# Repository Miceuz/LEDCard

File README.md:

LEDCard
=======

A business card with blinky leds

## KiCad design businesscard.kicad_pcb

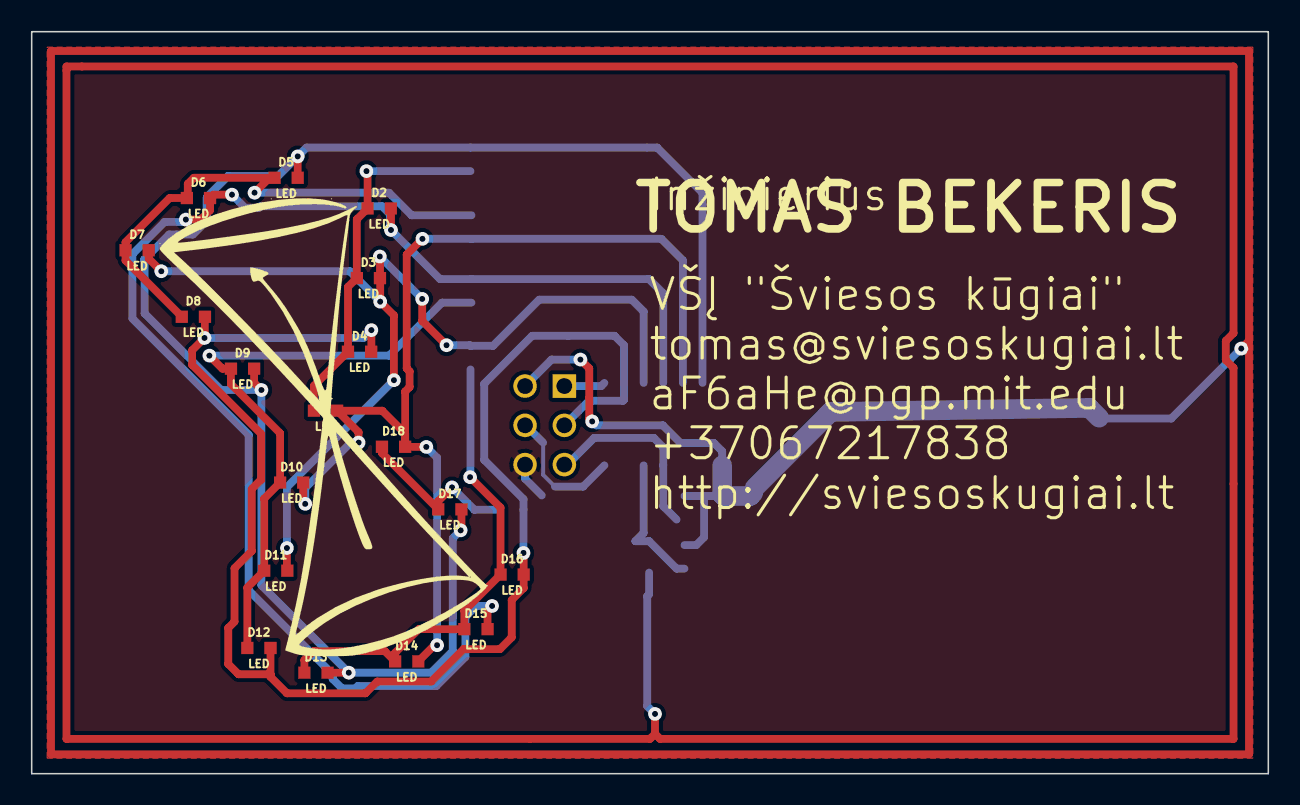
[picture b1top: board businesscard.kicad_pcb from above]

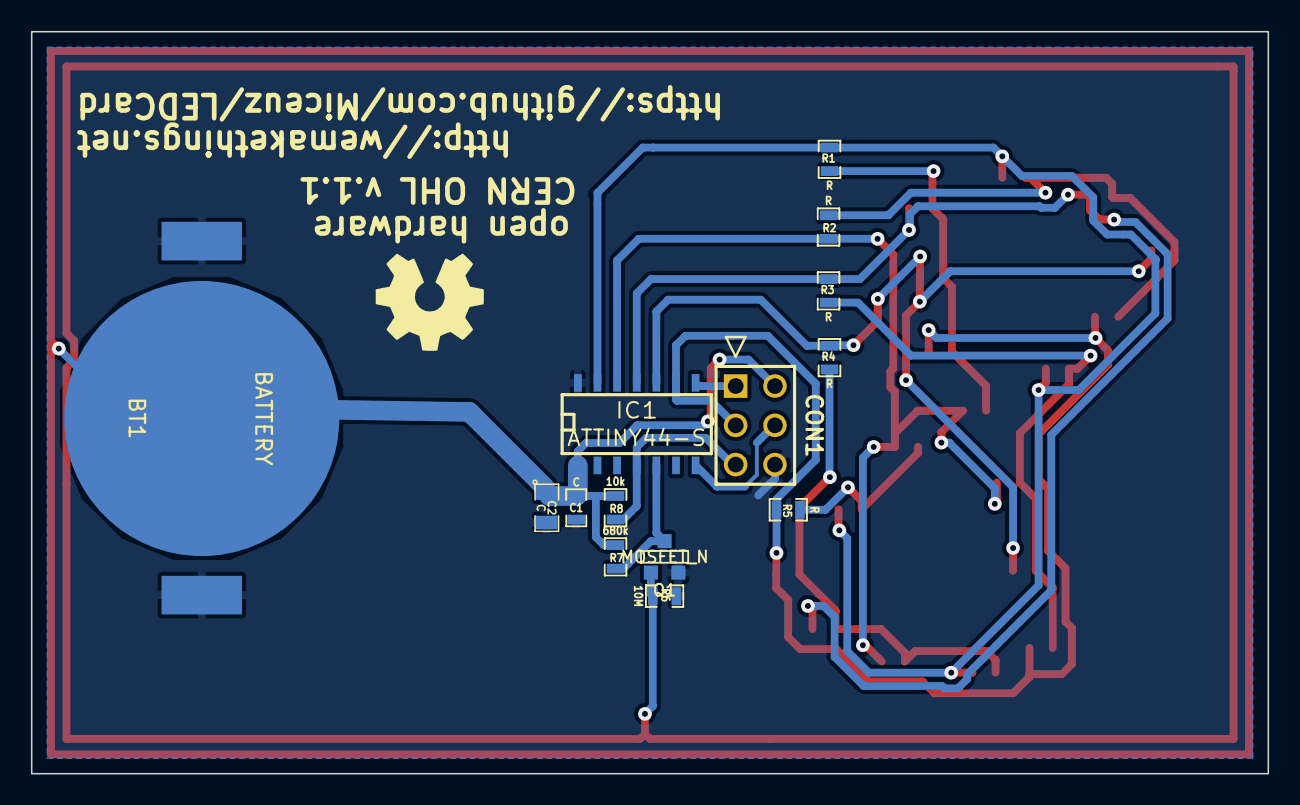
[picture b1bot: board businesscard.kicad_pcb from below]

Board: 2 copper layers, 80.0 x 48.0 mm, 32 parts (14 on the bottom side), 17 nets.

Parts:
BT1: BATTERY; BATT
C1: C; SM0603_Capa
C2: C; SM0805
CON1: AVR-ISP-6; avr-isp
D1, D2, D3, D4, D5, D6, D7, D8, D9, D10, D11, D12, D13, D14, D15, D16, D17, D18: LED; LED-0603-nosilk
IC1: ATTINY44-S; SO14E
Q1: MOSFET_N; SOT23GDS
R1, R2, R3, R4, R5: R; SM0603_Resistor
R6: 10M; SM0603_Resistor
R7: 680k; SM0603_Resistor
R8: 10k; SM0603_Resistor

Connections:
/WAKEUP: IC1.5, Q1.D, R7.2
GND: BT1.2, C1.2, C2.2, CON1.6, IC1.14, Q1.S, R6.2
unnamed: D17.1, D18.1, R5.1
unnamed: Q1.G, R6.1
unnamed: CON1.1, IC1.8
unnamed: CON1.4, IC1.7
unnamed: CON1.5, IC1.4, R8.2
unnamed: D2.2, D6.2, D15.2, IC1.11, R3.2
unnamed: D5.2, D9.2, D13.2, D17.2, IC1.13, R1.2
unnamed: D1.1, D2.1, D3.1, D4.1, R1.1
unnamed: D13.1, D14.1, D15.1, D16.1, R4.1
unnamed: D3.2, D7.2, D11.2, IC1.10, R4.2
unnamed: CON1.3, D4.2, D8.2, D12.2, D16.2, IC1.9, R5.2
unnamed: D5.1, D6.1, D7.1, D8.1, R2.1
unnamed: D9.1, D10.1, D11.1, D12.1, R3.1
unnamed: D1.2, D10.2, D14.2, D18.2, IC1.12, R2.2
VCC: BT1.1, C1.1, C2.1, CON1.2, IC1.1, R7.1, R8.1

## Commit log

2013-11-06 inital

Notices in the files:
businesscard.kicad_pcb:
CERN OHL v.1.1
